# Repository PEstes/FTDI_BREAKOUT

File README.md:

# FTDI_BREAKOUT

A full featured FTDI FT232R breakout board which features almost all UART pins(RX,TX,DTR,RTS,CTS) broken out and also IO voltage selection feature
to either 3.3v or 5v IO.

<br /><span xmlns:dct="http://purl.org/dc/terms/" property="dct:title">FTDI BREAKOUT</span> by <span xmlns:cc="http://creativecommons.org/ns#" property="cc:attributionName">NeutroN StrikeR</span> is licensed under a <a rel="license" href="http://creativecommons.org/licenses/by-sa/4.0/">Creative Commons Attribution-ShareAlike 4.0 International License</a>.

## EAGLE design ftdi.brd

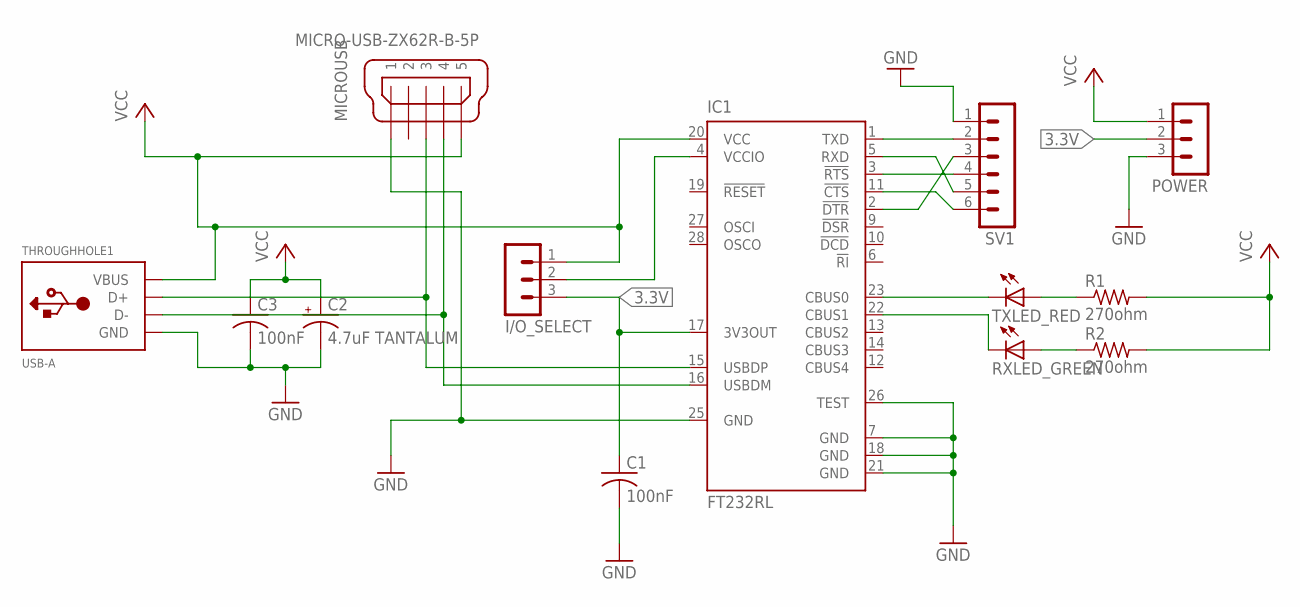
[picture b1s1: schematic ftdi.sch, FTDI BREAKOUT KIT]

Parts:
C1, C3: 100nF; C1206
C2: 4.7uF TANTALUM; C/6032-28R
I/O_SELECT: MA03-1
IC1: FT232RL; SSOP28
MICROUSB: MICRO-USB-ZX62R-B-5P; ZX62R-B-5P
POWER: MA03-1
R1, R2: 270ohm; R1206
RXLED_GREEN: LED3MM
SV1: MA06-1
THROUGHHOLE1: USB-A; MOLEX_480371000
TXLED_RED: LED3MM

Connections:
3.3V: C1.1, I/O_SELECT.3, IC1.17 (3V3OUT), POWER.2
GND: C1.2, C2.-, C3.2, IC1.7 (GND), IC1.18 (GND), IC1.21 (GND), IC1.25 (GND), IC1.26 (TEST), MICROUSB.1, POWER.3, SV1.1, THROUGHHOLE1.P$4 (GND)
unnamed: IC1.1 (TXD), SV1.2
unnamed: IC1.16 (USBDM), MICROUSB.4, THROUGHHOLE1.P$2 (D-)
unnamed: IC1.15 (USBDP), MICROUSB.3, THROUGHHOLE1.P$3 (D+)
unnamed: IC1.23 (CBUS0), TXLED_RED.K (C)
unnamed: I/O_SELECT.2, IC1.4 (VCCIO)
unnamed: R1.1, TXLED_RED.A
unnamed: R2.1, RXLED_GREEN.A
unnamed: IC1.2 (!DTR), SV1.3
unnamed: IC1.3 (!RTS), SV1.4
unnamed: IC1.5 (RXD), SV1.5
unnamed: IC1.11 (!CTS), SV1.6
RXLED_RED: IC1.22 (CBUS1), RXLED_GREEN.K (C)
VCC: C2.+, C3.1, I/O_SELECT.1, IC1.20 (VCC), MICROUSB.5, POWER.1, R1.2, R2.2, THROUGHHOLE1.P$1 (VBUS)

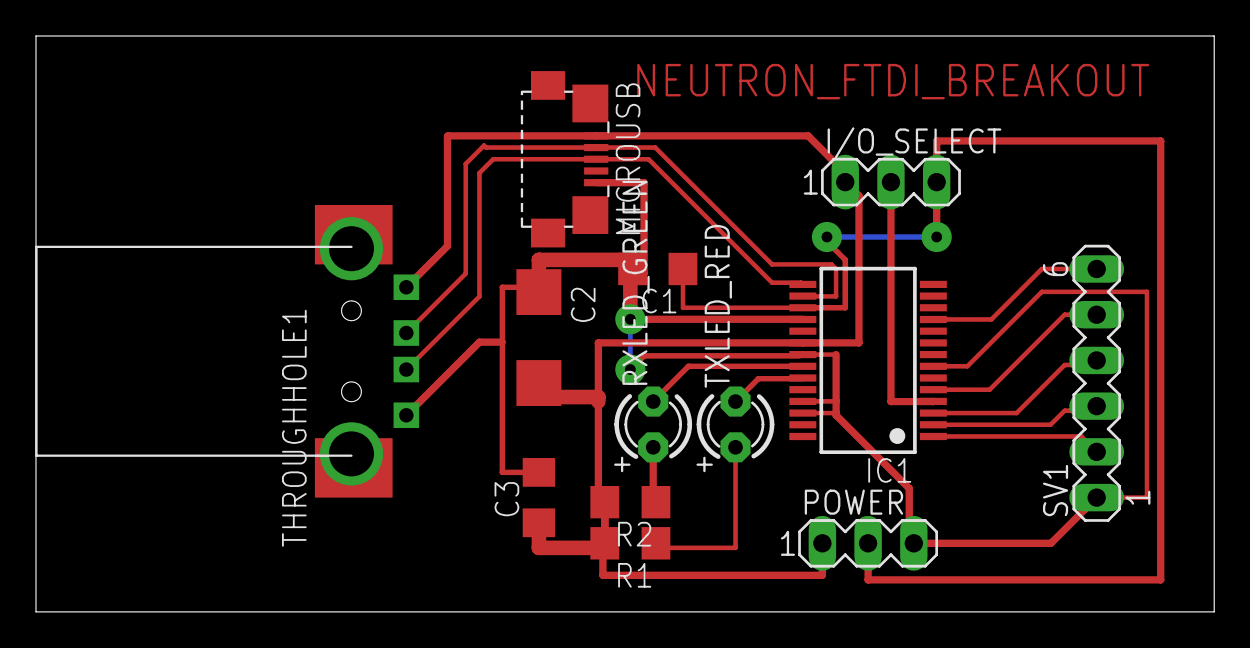
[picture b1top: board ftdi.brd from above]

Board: 2 copper layers, 65.5 x 32.0 mm, 13 parts (0 on the bottom side), 15 nets.

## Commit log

2015-01-08 :confetti_ball: Added .gitattributes & .gitignore files
2015-01-08 added files
